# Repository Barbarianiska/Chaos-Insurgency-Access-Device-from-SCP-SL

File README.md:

# Chaos Insurgency Access Device from SCP: Secret Laboratory

<pre>
  <div align="center">
     $$$$$$\  $$\   $$\  $$$$$$\  $$\   $$\ $$$$$$$$\ 
    $$  __$$\ $$$\  $$ |$$  __$$\ $$ | $$  |$$  _____|
    $$ /  \__|$$$$\ $$ |$$ /  $$ |$$ |$$  / $$ |      
    \$$$$$$\  $$ $$\$$ |$$$$$$$$ |$$$$$  /  $$$$$\    
     \____$$\ $$ \$$$$ |$$  __$$ |$$  $$<   $$  __|   
    $$\   $$ |$$ |\$$$ |$$ |  $$ |$$ |\$$\  $$ |      
    \$$$$$$  |$$ | \$$ |$$ |  $$ |$$ | \$$\ $$$$$$$$\ 
     \______/ \__|  \__|\__|  \__|\__|  \__|\________|

    ▒▒▒▒▒▒▒▒▒▒▒▒▒▒▒▒▒▒▒▒▒▒▒▒▒▒▒▒▒░░░░░░░░░░░░░░░░░░░░░
    EMERGENCY STRESS-MITIGATION SOFTWARE BOOTING UP...
  </div>
</pre>
      
This is a repository with files containing instructions on making a device similar to one found in the game SCP: Secret Laboratory by Northwood

## Progress bar

### Device body

- [ ] 3D model (depends on the internal components, almost ready)
- [ ] Print 3D model

### Components

- [x] Microcontroller ESP32
- [x] Gamepad crosspiece
- [ ] Buttons
- [x] Display
- [ ] Accumulator
- [ ] USB cable
- [x] LEDs
- [x] RFID reader

### Board Piece

- [ ] KiCAD model etc...

### Firmware

#### Common functions

- [ ] RFID reader
- [ ] LED control

#### Game

- [x] Basic bool map model (Windows console version)
- [x] Basic ESP32 realisation with 2'8 TFT display 240x320 and keypad (button matrix)
- [x] Add sprites for snake movements
- [x] Add score counter
- [x] Add loading display
- [ ] Change random generator function
- [ ] Lose snake animation

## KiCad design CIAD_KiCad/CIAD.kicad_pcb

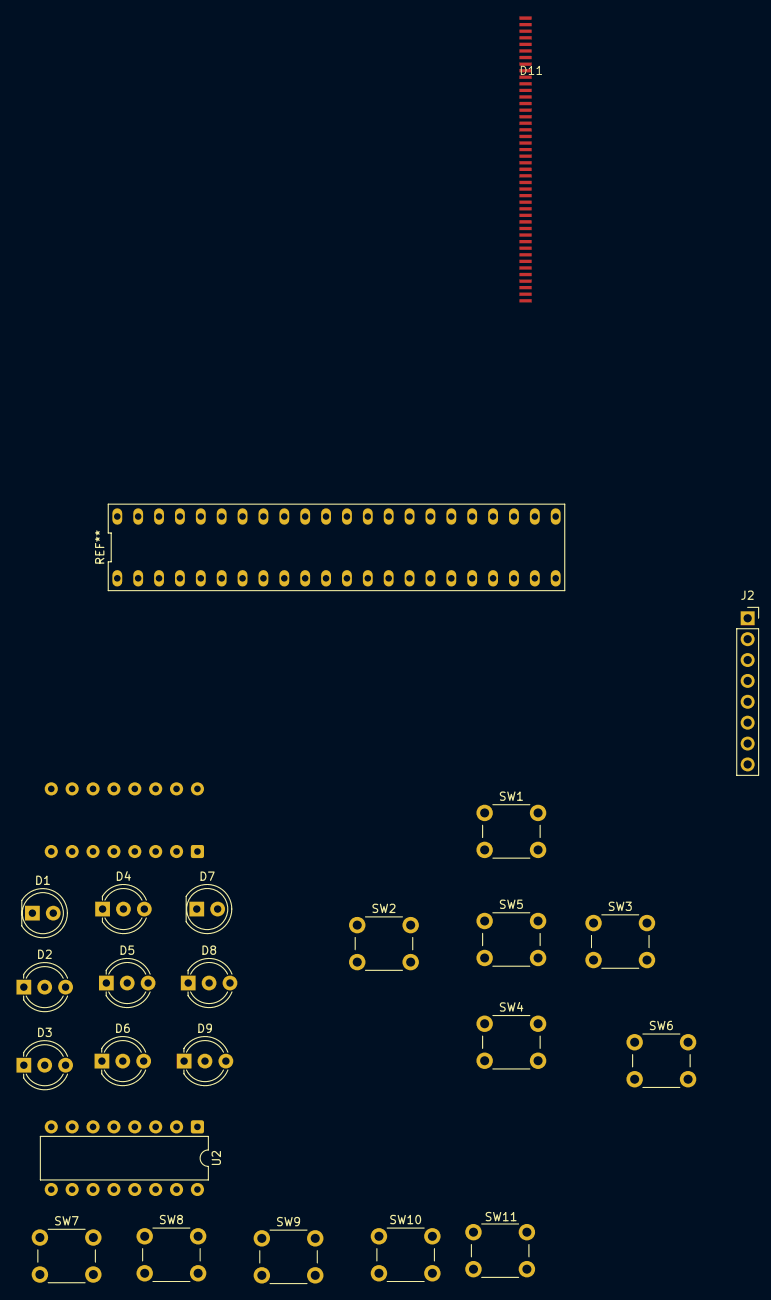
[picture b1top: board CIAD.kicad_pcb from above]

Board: 2 copper layers, 24 parts (1 on the bottom side), 17 nets, no tracks yet.

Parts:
D1, D7: LED; LED_D5.0mm
D2, D3, D4, D5, D6, D8, D9: LED_Dual_AKA; LED_D5.0mm-3
D11: 44pin_screen
J2: Conn_01x08; PinSocket_1x08_P2.54mm_Vertical
SW1, SW2, SW3, SW4, SW5, SW6, SW7, SW8, SW9, SW10, SW11: SW_Push; SW_PUSH_6mm_H4.3mm
U1, U2: 74HC595; DIP-16_W7.62mm

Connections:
/LED1: D1.2 (A), U1.7 (QH)
/LED2_B: D2.3 (A2), U1.5 (QF)
/LED2_G: D2.1 (A1), U1.6 (QG)
/LED3_B: D3.3 (A2), U2.6 (QG)
/LED3_G: D3.1 (A1), U2.7 (QH)
/LED4_B: D4.3 (A2), U1.3 (QD)
/LED4_G: D4.1 (A1), U1.4 (QE)
/LED5_B: D5.3 (A2), U1.1 (QB)
/LED5_G: D5.1 (A1), U1.2 (QC)
/LED6_B: D6.3 (A2), U2.4 (QE)
/LED6_G: D6.1 (A1), U2.5 (QF)
/LED7: D7.2 (A), U1.15 (QA)
/LED8_B: D8.3 (A2), U2.2 (QC)
/LED8_G: D8.1 (A1), U2.3 (QD)
/LED9_B: D9.3 (A2), U2.15 (QA)
/LED9_G: D9.1 (A1), U2.1 (QB)
GND: D1.1 (K), D2.2 (K), D3.2 (K), D4.2 (K), D5.2 (K), D6.2 (K), D7.1 (K), D8.2 (K), D9.2 (K), J2.3, U1.8 (GND), U2.8 (GND)

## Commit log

2026-03-18 First iteration, added templates for the firmware and hardware
2026-03-18 README quickfix
2026-03-25 Added new libraries for hardware, updated the hardware part
2026-03-25 updated .gitignore, replaced LEDs in /hardware and fixed connections
2026-04-03 small updates to hardware
2026-05-11 Update README.md
    Taskbar adjusting
2026-05-11 Create README.md in "Firmware" directory
2026-05-11 Almost complete SNAKE game firmware adding
